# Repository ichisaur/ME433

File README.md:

# Ichi's Advanced Mechatronics Corner
## Go away Ethan.

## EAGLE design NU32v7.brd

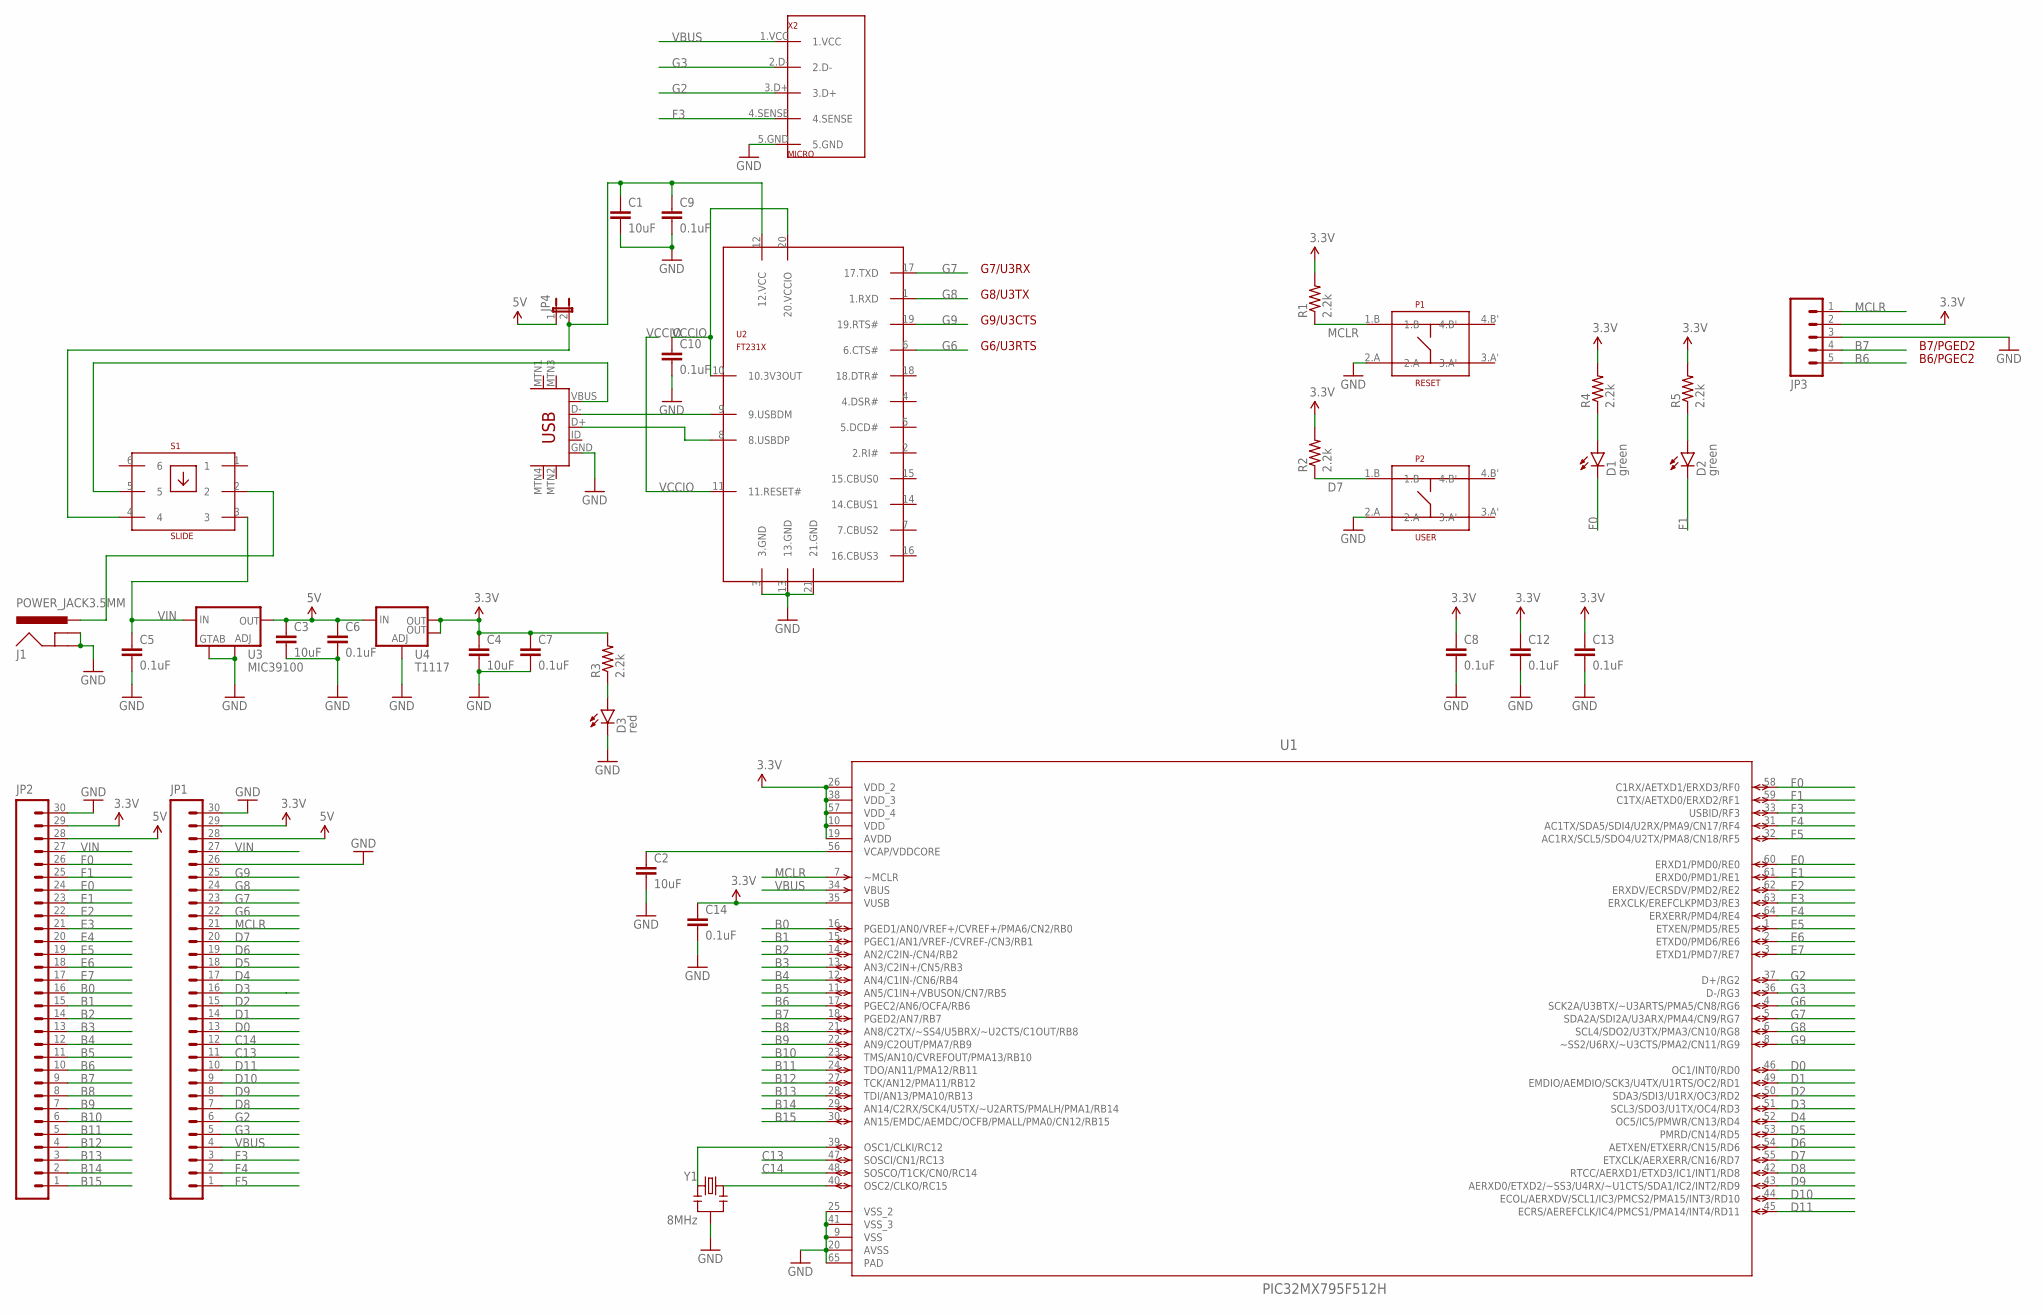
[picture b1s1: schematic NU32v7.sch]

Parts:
C1, C2, C3, C4: 10uF; 0603-CAP
C5, C6, C7, C8, C9, C10, C12, C13, C14: 0.1uF; 0603-CAP
D1, D2: green; LED-0603
D3: red; LED-0603
J1: POWER_JACK3.5MM; POWER_JACK_3.5MM
JP1, JP2: M30NO_SILK; 1X30_NO_SILK
JP3: M05PTH; 1X05
JP4: JUMPER-2SMD-NO; SJ_2S-NO
P1: RESET; MOM_SW
P2: USER; MOM_SW
R1, R2, R3, R4, R5: 2.2k; 0603-RES
S1: SLIDE; SLIDE_SW
U1: PIC32MX795F512H; QFN50P900X900X100-65N
U2: FT231X; QFN50P400X400X100-21N
U3: MIC39100; SOT223
U4: T1117; SOT223
X1: MINI; USB-MINIB
X2: MICRO; MICROUSB
Y1: 8MHz; RESONATOR-SMD

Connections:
3.3V: C4.1, C7.1, C8.1, C12.1, C13.1, C14.1, JP1.29, JP2.29, JP3.2, R1.2, R2.2, R3.2, R4.2, R5.2, U1.10 (VDD), U1.19 (AVDD), U1.26 (VDD_2), U1.35 (VUSB), U1.38 (VDD_3), U1.57 (VDD_4), U4.2 (OUT), U4.4 (OUT)
5V: C3.1, C6.1, JP1.28, JP2.28, JP4.1, U3.3 (OUT), U4.3 (IN)
B0: JP2.16, U1.16 (PGED1/AN0/VREF+/CVREF+/PMA6/CN2/RB0)
B1: JP2.15, U1.15 (PGEC1/AN1/VREF-/CVREF-/CN3/RB1)
B2: JP2.14, U1.14 (AN2/C2IN-/CN4/RB2)
B3: JP2.13, U1.13 (AN3/C2IN+/CN5/RB3)
B4: JP2.12, U1.12 (AN4/C1IN-/CN6/RB4)
B5: JP2.11, U1.11 (AN5/C1IN+/VBUSON/CN7/RB5)
B6: JP2.10, JP3.5, U1.17 (PGEC2/AN6/OCFA/RB6)
B7: JP2.9, JP3.4, U1.18 (PGED2/AN7/RB7)
B8: JP2.8, U1.21 (AN8/C2TX/~SS4/U5BRX/~U2CTS/C1OUT/RB8)
B9: JP2.7, U1.22 (AN9/C2OUT/PMA7/RB9)
B10: JP2.6, U1.23 (TMS/AN10/CVREFOUT/PMA13/RB10)
B11: JP2.5, U1.24 (TDO/AN11/PMA12/RB11)
B12: JP2.4, U1.27 (TCK/AN12/PMA11/RB12)
B13: JP2.3, U1.28 (TDI/AN13/PMA10/RB13)
B14: JP2.2, U1.29 (AN14/C2RX/SCK4/U5TX/~U2ARTS/PMALH/PMA1/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)
B15: JP2.1, U1.30 (AN15/EMDC/AEMDC/OCFB/PMALL/PMA0/CN12/RB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)
C13: JP1.11, U1.47 (SOSCI/CN1/RC13)
C14: JP1.12, U1.48 (SOSCO/T1CK/CN0/RC14)
D0: JP1.13, U1.46 (OC1/INT0/RD0)
D1: JP1.14, U1.49 (EMDIO/AEMDIO/SCK3/U4TX/U1RTS/OC2/RD1)
D2: JP1.15, U1.50 (SDA3/SDI3/U1RX/OC3/RD2)
D3: JP1.16, U1.51 (SCL3/SDO3/U1TX/OC4/RD3)
D4: JP1.17, U1.52 (OC5/IC5/PMWR/CN13/RD4)
D5: JP1.18, U1.53 (PMRD/CN14/RD5)
D6: JP1.19, U1.54 (AETXEN/ETXERR/CN15/RD6)
D7: JP1.20, P2.1.B, R2.1, U1.55 (ETXCLK/AERXERR/CN16/RD7)
D8: JP1.7, U1.42 (RTCC/AERXD1/ETXD3/IC1/INT1/RD8)
D9: JP1.8, U1.43 (AERXD0/ETXD2/~SS3/U4RX/~U1CTS/SDA1/IC2/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)
D10: JP1.9, U1.44 (ECOL/AERXDV/SCL1/IC3/PMCS2/PMA15/INT3/R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)
D11: JP1.10, U1.45 (ECRS/AEREFCLK/IC4/PMCS1/PMA14/INT4/RD11)
E0: JP2.24, U1.60 (ERXD1/PMD0/RE0)
E1: JP2.23, U1.61 (ERXD0/PMD1/RE1)
E2: JP2.22, U1.62 (ERXDV/ECRSDV/PMD2/RE2)
E3: JP2.21, U1.63 (ERXCLK/EREFCLKPMD3/RE3)
E4: JP2.20, U1.64 (ERXERR/PMD4/RE4)
E5: JP2.19, U1.1 (ETXEN/PMD5/RE5)
E6: JP2.18, U1.2 (ETXD0/PMD6/RE6)
E7: JP2.17, U1.3 (ETXD1/PMD7/RE7)
F0: D1.C, JP2.26, U1.58 (C1RX/AETXD1/ERXD3/RF0)
F1: D2.C, JP2.25, U1.59 (C1TX/AETXD0/ERXD2/RF1)
F3: JP1.3, U1.33 (USBID/RF3), X2.4.SENSE
F4: JP1.2, U1.31 (AC1TX/SDA5/SDI4/U2RX/PMA9/CN17/RF4)
F5: JP1.1, U1.32 (AC1RX/SCL5/SDO4/U2TX/PMA8/CN18/RF5)
G2: JP1.6, U1.37 (D+/RG2), X2.3.D+
G3: JP1.5, U1.36 (D-/RG3), X2.2.D-
G6: JP1.22, U1.4 (SCK2A/U3BTX/~U3ARTS/PMA5/CN8/RG6), U2.6 (6.CTS#)
G7: JP1.23, U1.5 (SDA2A/SDI2A/U3ARX/PMA4/CN9/RG7), U2.17 (17.TXD)
G8: JP1.24, U1.6 (SCL4/SDO2/U3TX/PMA3/CN10/RG8), U2.1 (1.RXD)
G9: JP1.25, U1.8 (~SS2/U6RX/~U3CTS/PMA2/CN11/RG9), U2.19 (19.RTS#)
GND: C1.2, C2.2, C3.2, C4.2, C5.2, C6.2, C7.2, C8.2, C9.2, C10.2, C12.2, C13.2, C14.2, D3.C, J1.2.GND (GND), J1.3.GNDBREAK (GNDBREAK), JP1.26, JP1.30, JP2.30, JP3.3, P1.2.A, P2.2.A, U1.9 (VSS), U1.20 (AVSS), U1.25 (VSS_2), U1.41 (VSS_3), U1.65 (PAD), U2.3 (3.GND), U2.13 (13.GND), U2.21 (21.GND), U3.2 (ADJ), U3.4 (TAB), U4.1 (ADJ), X1.GND, X2.5.GND, Y1.2
MCLR: JP1.21, JP3.1, P1.1.B, R1.1, U1.7 (~MCLR)
unnamed: U1.40 (OSC2/CLKO/RC15), Y1.1
unnamed: U1.39 (OSC1/CLKI/RC12), Y1.3
unnamed: C2.1, U1.56 (VCAP/VDDCORE)
unnamed: S1.5, X1.VBUS
unnamed: U2.9 (9.USBDM), X1.D-
unnamed: U2.8 (8.USBDP), X1.D+
unnamed: J1.1.POWER (PWR), S1.2
unnamed: D3.A, R3.1
unnamed: C1.1, C9.1, JP4.2, S1.4, U2.12 (12.VCC)
unnamed: D1.A, R4.1
unnamed: D2.A, R5.1
VBUS: JP1.4, U1.34 (VBUS), X2.1.VCC
VCCIO: C10.1, U2.10 (10.3V3OUT), U2.11 (11.RESET#), U2.20 (20.VCCIO)
VIN: C5.1, JP1.27, JP2.27, S1.3, U3.1 (IN)

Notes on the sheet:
G6/U3RTS
G9/U3CTS
G8/U3TX
G7/U3RX
B7/PGED2
B6/PGEC2

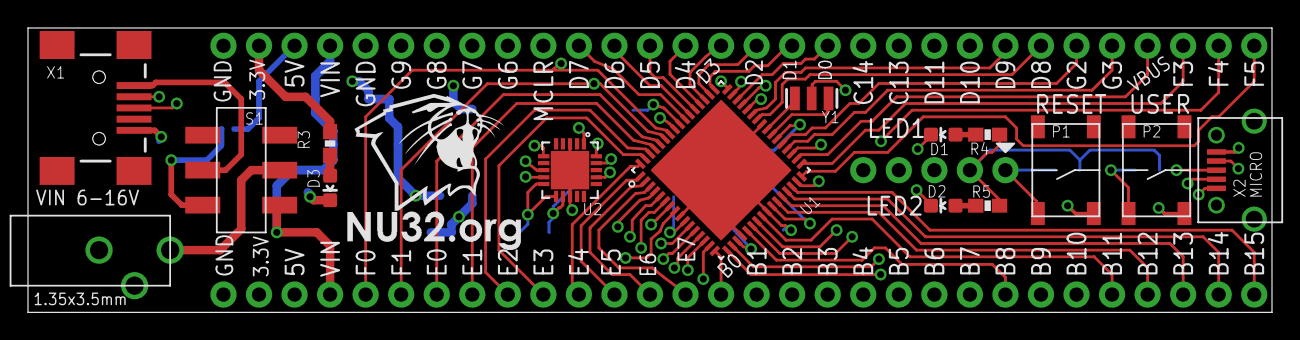
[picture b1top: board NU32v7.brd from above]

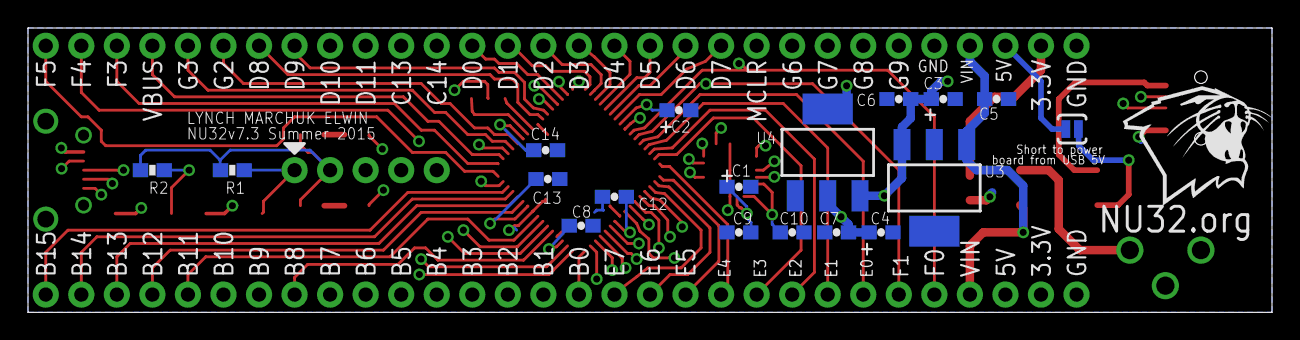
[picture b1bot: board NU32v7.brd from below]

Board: 2 copper layers, 88.9 x 20.3 mm, 36 parts (18 on the bottom side), 67 nets.

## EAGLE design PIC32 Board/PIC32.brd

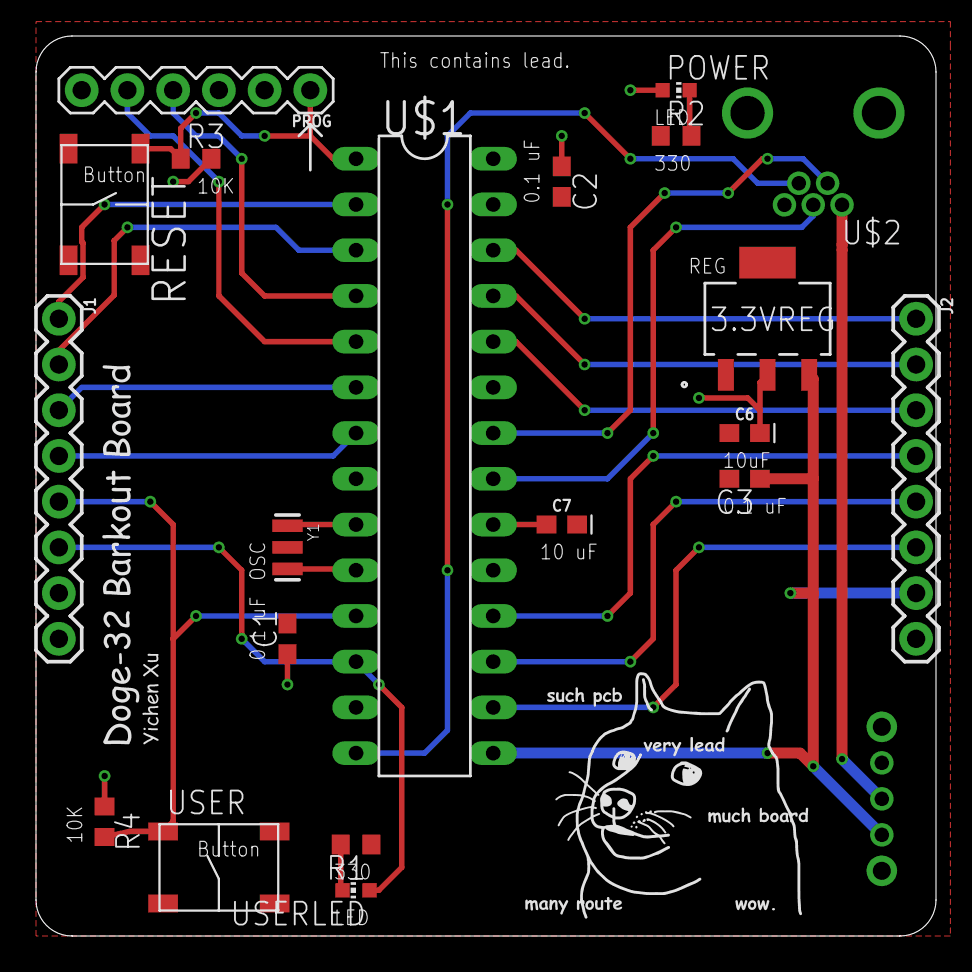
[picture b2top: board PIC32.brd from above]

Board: 2 copper layers, 50.0 x 50.0 mm, 21 parts (0 on the bottom side), 27 nets.

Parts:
3.3VREG: TLV1117-33CDCYR; DCY4
C1, C2, C3: 0.1uF; C0603
C6, C7: 10uF; 0603-POLAR
J1, J2: 1X08
MCLR: NU32V7_MOM_SW
POWER: Red; CHIP-LED0603
POWERSWITCH: SLIDE_SWITCH
PROG: 1X06_NO_SILK
R1, R2: 330; R0603
R3, R4: 10k; R0603
U$1: PIC32; DIL28-3
U$2: USB_MINI; USB-MB-H
USER: NU32V7_MOM_SW
USERLED: Green; CHIP-LED0603
Y1: RESONATORSMD; RESONATOR-SMD

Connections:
3.3V: 3.3VREG.2, C1.1, C2.1, C6.+, J1.7, POWER.A, PROG.2, R3.2, R4.1, U$1.13, U$1.23, U$1.28
5V: 3.3VREG.3, C3.1, J2.7, POWERSWITCH.OUT2, U$1.15
A0: J1.1, U$1.2
A1: J1.2, U$1.3
A4: J1.6, U$1.12, USERLED.A
B2: J1.3, U$1.6
B3: J1.4, U$1.7
B4: J1.5, R4.2, U$1.11, USER.1.B
B7: J2.6, U$1.16
B8: J2.5, U$1.17
B9: J2.4, U$1.18
B13: J2.3, U$1.24
B14: J2.2, U$1.25
B15: J2.1, U$1.26
D+: U$1.21, U$2.D+
D-: U$1.22, U$2.D-
GND: 3.3VREG.1, C1.2, C2.2, C3.2, C6.-, C7.+, J1.8, J2.8, MCLR.2.A, PROG.3, R1.1, R2.1, U$1.8, U$1.19, U$1.27, U$2.GND, USER.2.A, Y1.2
MCLR: MCLR.1.B, PROG.1, R3.1, U$1.1
unnamed: U$1.10, Y1.3
unnamed: C7.-, U$1.20
unnamed: U$1.9, Y1.1
unnamed: POWER.C, R2.2
unnamed: R1.2, USERLED.C
PGC: PROG.4, U$1.4
PGD: PROG.5, U$1.5
USBID: U$1.14, U$2.ID
VBUS: POWERSWITCH.IN, U$2.VBUS

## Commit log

2018-04-10 HW1 initial commit
2018-04-10 main.c initial commit
2018-04-10 Configured Pragma Values
2018-04-10 Light up green LED
2018-04-10 Implemented button control. Reorganized Git Repo
2018-04-10 add photos
2018-04-10 Cleanup and comment code
2018-04-10 Board initial commit
2018-04-15 routine commit
2018-04-17 finished board
2018-04-17 merged gerbers
2018-04-17 fix random silkscreen issues
2018-04-19 Create HW4 file
2018-04-19 fixed build issues. Verified constant outputs
2018-04-19 Remove redundant files
2018-04-19 implement sine wave
2018-04-19 proof of completion
2018-04-19 Remove exactly one uneccessary variable
2018-04-19 The last commit was wrong. Turns out there were two uneccesary variables
2018-04-25 Homework 5 initial commit
2018-04-25 initial expander helper code
2018-04-25 changed i2c1 to i2c2 in helper
2018-04-25 finish hw 5
2018-04-25 include circuit diagram
2018-04-28 Initial commit Homework 6, fix lookup mixup, fix for loop init
2018-04-28 Add drawBox function
2018-04-28 Implement progress bar
2018-04-28 Fix infinite loop
2018-04-28 Add FPS counter
2018-05-07 HW 7 and 8 directores create
2018-05-07 Add dependencies and functions from previous files
2018-05-07 Verify WhoAmI
2018-05-07 Add multi read i2c
2018-05-07 Add get data from IMU
2018-05-07 streamlined while loop
2018-05-07 Add bars
2018-05-08 Blink Harmony created
2018-05-08 Add imuHarmony
2018-05-15 Homework 12
2018-05-22 Add serial port code
2018-05-22 Homework 9 done
2018-05-22 Whoops fixed timing
2018-05-22 Filters!
2018-05-22 Homework 11
2018-05-29 IDK what this is....
2018-05-29 Sync commits
2018-05-29 Homework 13
2018-05-29 Create pic side
2018-05-29 Android App Completed
2018-06-11 Homework 15
2018-06-12 Homework 16 commit
2018-06-12 Homework 17
2018-06-12 Sensor Code
2018-06-12 pic code
2018-06-12 Debugging COM ports
2018-06-12 Verified com port works and echos
2018-06-12 Tested motor speeds. Modified to be open loop design
2018-06-12 Well its turning in the direction of the line in an uncontrolled manner
2018-06-12 Realized PI controller was all wrong and tried to rewrite only to realize none of it makes sense
2018-06-14 Bit of tuning

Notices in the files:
parts and their libraries:
SparkFun-Connectors: Licensing: Creative Commons ShareAlike 4.0 International - https://creativecommons.org/licenses/by-sa/4.0
SparkFun: Licensing: CC v3.0 Share-Alike You are welcome to use this library for commercial purposes.
